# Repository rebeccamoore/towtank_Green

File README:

Section 1: An Introduction

This document serves as a comprehensive instruction manual for using the large tow-tank system in Link 280 at Syracuse University.  In this document, you will find descriptions of hardware and software.  It is the goal to establish this using some type of revision software.  The original document was maintained on github @ github.com/johndannenhoffer.

1.1: Document use

This document serves as a simple instruction manual for using the large tow-tank system in Link 280 at Syracuse University.  This was originally prepared by John Dannenhoffer IV.  To make changes, please indicate your name and contact information in the authors list (below) and specify which sections you contributed (and at what time these contributions were made).  If you have any questions regarding material, please direct your questions towards the most recent author of a section.  

1.1.2: Comments and plans for revision
Comments or plans for revisions will be presented using c-style comments.  This means that lines are commented using "//" and whole blocks of comments are denoted using a leading "/*" and a trailing "*/"

E.G.
This is a fake section to show commenting conventions used in this document.
//If you would like to commend a line, do so like this.

This is a list of things that will change over time.  So far we have…
foo
bar
foobar
/* this is something I plan to add later and finalize, but isn't currently finished yet
This is also something that should be continued */

1.1.3: Revision control software

By using revision control software, a document that goes through a number of changes can be maintained such that if undesirable changes are made, one can go back to previous versions.  Also, size is reduced by not having to keep archived files.  A free and easy to use software that implements revision control is Git and it's website github.com.  NOTE: To be free, an accounts material must remain open to the public.  This may be undesirable in the future.  There are two ways to use this software.  You can either download git to your local computer and manage your files (called repositories) that way or you can upload and download content through the web while logged into your account.

Branching: To change a document for your own purposes, create a branch from some node of the project.  Go to github.com to learn about this process.

Section 1.2 Authors

John Dannenhoffer IV (JFD4)
315-256-3521
johndannenhoffer@gmail.com

Summer research student for the summer of 2012.  Original author

Revision History
8/20/2012 - Created document and added sections 1,2,3, and 4 (JFD4)
//10/6/2012 - Added pictures of hardware (JFD4)

Section 1.2: Contents

This document contains a number of sections which describe different parts of the system (hardware, software, instructions,...)

1. Introduction:  Describes the use and maintenance of this document and its contents.

2. Running the tow tank:  A quick how-to guide to operating the tow tank.

3. Tow tank hardware:  The main hardware components are explained here

4. Tow tank software. The software used to run and gather data from the tow tank is described here

/* To be added later
5. PIV.  The components used for flow visualization are described here

6. Beginning Electronics for Experimentalists: This serves as a guide to electronics for experimentalists, especially those not 

7. Instrumentation for Experimentalists: A brief description of instrumentation techniques useful for the experimentalist.  This and the next section are geared towards experimentalists working in fluid mechanics

8. Actuation for Experimentalists: A description of actuation techniques useful for the experimentalist.  Microcontrollers, DC Motors, solenoids, servos, LEDs, MOSFETs and H-Bridge drivers, amplifiers, and much more will be discussed.  This section, along with sections 5 can serve as a guide to designing actuation system for experimental use.

9. Electronics Fabrication for Experimentalist:  This section describes experiential knowledge on different techniques to setup electronic apparatus for use in a lab setting.  Breadboarding, prototyping, soldering, and PCB (printed circuit board) production are discussed.

10. Purchasing: Specific vendors and purchasing techniques for everything electronic are discussed here.  Take this section with a grain of salt, as the electronics landscape changes very quickly.

*/

Section 2: Running the tow tank

This section describes the basics of running the tow tank.

2.1: What is needed to run the tow tank?

To run the tow tank, the following is needed to run the tow tank.

-Arduino hardware.  An Arduino is a micro controller development board which is used for quick prototyping of embedded systems.  Digital and analog signals from hardware can interfaced with software written in an easy to write c-based language.  The Arduino board (there are a number of generations of boards with slight differences) has header pin outputs for almost all of its pins.  This allows the user to connect peripherals to the Arduino such a digital signals, analog signals, serial signals, power,…  The board that was used for the first generation of the tow tank was the Arduino Uno.  Also, because there is a large Arduino community, a number of open source hardware and software tools have been developed.  Supplementary hardware which are attached on top of an Arduino are called shields.  These can serve many purposes.  Also, a number of software libraries have been developed to do various things within software, such as numerical calculations, interfacing with certain hardware,…  This project uses one shield (below) and its corresponding library.

-Arduino Software.  This is software that is used to communicate between a computer and the micro controller development board (Arduino).  Go to http://arduino.cc/en/Main/Software to download the latests version of the software. The Arduino software contains three important things.  1) An IDE (integrated development environment) to write and compile code in. 2) Drivers to communicate with the Arduino.  This allows you to upload your code onto the board.  It also allows for serial communication. 3) A serial monitor.  This allows the user to monitor the serial communication between the Arduino hardware and the computer.  This can be used very effectively as a debugging tool.

-A power source.  You need a way to power the power electronics in the tow tank system.  An ATX power supply and breakout board is used for this purpose.

-Pololu motor driver shield.  This "shield" is used in order to allow an Arduino to switch large amounts of current on an off.  http://www.pololu.com/catalog/product/2502  .  This shield plugs into the Arduino on top (it will only fit one way).  Through the connections with the Arduino, the program running on the Arduino controls the hardware on the shield and through this hardware, can control large amounts of current.  We use this to drive the motors for the tow tank.

-Pololu motor driver shield library.  To control the motor driver shield, software needs to be written on the Arduino.  Because interfacing with the shield is not trivial, a software library has been developed to make interfacing with the shield easier.  This allows simple function calls in your code to control the shield.  Go to https://github.com/pololu/Dual-VNH5019-Motor-Shield to download the zip file (click the "zip" button next to the "http" button.   Unzip this file.  Move the folder "DualVNH5019MotorShield" to the appropriate folder which holds your Arduino libraries.  On a mac, the directory would be ~/Documents/Arduino/libraries/. On Windows, it would be My Documents\Arduino\libraries .  NOTE:  If this is the first library that you are adding, you may need to create the "libraries" folder in the appropriate place.  When you launch the Arduino application, and you click the "Sketch" drop down and "Import Libraries", you should see the DualVNH5019-Motor-Shield as an option.  If you click this, it should add the line #include "DualVNH5019-Motor-Shield.h" to the top of your code.

-(OPTIONAL) Direction control board.  To prevent the system from causing itself harm by running the carriage into one of the sides, a control board was developed which uses 2 limit switches to limit motion.  If a limit switch is pressed, the carriage is stopped from moving in the direction of that limit switch, but can still move in the opposite direction.  See section 3.2.5 for more information on this.

2.2.1: Steps to run the tow tank w/o direction control.

Below are step by step instructions for setting up and running the tow tank.

1) Power source.  Make sure the power source is working.  Plug the 24-pin connector from the ATX power supply into the distribution board (the header is polarized).  Plug the power supply into a wall outlet and turn it on.  The fan should turn on.  NOTE: If you are using a first generation power distribution board (REV 1.0), you will need to solder together the green wire with one of the black wires.  /*This is addressed in later revisions of the boards.*/

2) Check power.  If the fan turns on, check the voltage levels of each of the outputs.  The power supply will output 4 different levels: Ground (GND), 3.3 volts (3V3), 5 volts (5V), and 12 volts (12V).  Using a multimeter in voltage mode, press the black probe to any exposed metal on the ground rail (lines denote which terminal blocks (green things) and barrier strips (black things) belong to which rail).  I suggest pressing the black probe to one of the screws in a ground (GND) terminal block.  Then take the red probe and connect it to the different rails.  The meter should read out approximately 3.3, 5.0 and 12.0 volts.  The board allows for higher voltages to be achieved by "stacking."  Refer to Section 3.2.4 for more information of this.

3) If the power is working (the fan turns on and the voltage levels seems to be correct), connect power to the motor driver shield.  To do this, connect the 12V on the power distro to the VIN of the motor driver shield and the GND to the GND.  Do this using a wire with stripped ends and the terminal blocks.  A blue LED should turn on.

4) Connect the motor to channel 1 of the motor driver shield.  Connect the output of the motor (the gray cable) to a barrier strip.  The gray cable has two spade terminal outputs.  Connect these to the long barrier strip on different strips (not across from each other).  A barrier strip connects the two connections in the same row.  From the barrier strip, connect the motor to the motor shield using a cable with a spade terminal on one end and a stripped wire on the other end.  The positive motor connection (red) should be connected to the M1A terminal connection.  The negative motor connection (black) should be connected to the M1B terminal connection.

NOTE: Using "beep" mode on the multimeter checks to see if connections are made.  The multimeter will emit a beep if a short is detected between the two probes.  This is extremely useful for checking to see if connections are securely made.

Use the multimeter to check that the positive terminal of the motor is connected to the M1A terminal and the negative terminal of the motor is connected to the M1B terminal.

IMPORTANT NOTE: IN BEGINNING TESTING, IT IS IMPORTANT TO MAKE SURE THAT THE SYSTEM DOESN'T BREAK ITSELF.  THIS MEANS THAT YOU SHOULD HAVE YOUR HAND ON THE POWER SUPPLY SWITCH DURING TESTING AND IF THE CARRIAGE APPROACHES A SIDE, TURN OFF THE POWER.  THIS IS ADDRESSED LATER WITH THE USE OF DIRECTION LIMITING CIRCUITS AND LIMIT SWITCHES, BUT UNTIL THOSE ARE PUT IN THE SYSTEM, PROCEED WITH CAUTION.

5) Test the motor.  Open the sketch (programs in Arduino are called sketches) called demo.pde (could be called demo.ino based on your version of the Arduino software downloaded).  This is in the pololu library zip file.  Connect the Arduino to the computer via USB cable (a light should go on on the Arduino) and click the upload button in the Arduino IDE (any compiling errors should be trivial and easily addressable).

6) "Plug" the shield into the Arduino.  This should fit only one way.

7) When the sketch is done uploading to the board (the yellow RX LED will flash while code is being uploaded onto the board), the system should start moving in the manner implemented in demo.pde.  The default (if you don't change any of the code) is to go one direction for ~1 second, speeding up along the way.  Then slow down for ~1 second to 0.  Then do the same thing in the opposite direction.  The motor should then stop for ~4 seconds.  This will then repeat.

2.2.2 Steps for running the tow tank w/ direction control:

Once the operation of the system is verified w/o direction control, implement the direction control.  This uses the direction control boards (small ~5cmx~5cm boards with 2 relays and other components) and 2 limit switches.

The steps for doing this are basically the same, but with 1 difference.  The motor must be put in series with the direction control circuit.  The workings of this control circuit are described in section 3.2.? but the basic idea is that if a limit switch is depressed, the motor can not move in a direction that would damage the system.  

To do this, take the connection between M1A and the barrier strip and "insert" the direction control circuit in this connection.

The only connection that is different for this setup is the connection between M1A and the barrier strip.  The new connections should be as follows.

-The positive terminal on the barrier strip (red spade terminal) should be connected to the CON1 screw terminal on the direction control board.  
-The CON2 screw terminal should be connected to the M1A connection on the motor driver shield.  
-Connect 12V and Ground to the board's screw terminal power connections.  

The board will allow current to flow only if the connection to the limit switch is closed (connected).  The connections to the limit switches are one the 4x1 header pin on the direction control board.  The 1 and 2 pins control 1 direction and the 3 and 4 pins control the other direction.  The wiring for this connector is described in Section 3.2.5

This means that to move in both directions, both 1 and 2 as well as 3 and 4 should be shorted.  To test this (without connecting the limit switches), use some metal object to short pins 1 and 2 and pins 3 and 4 (NOTE: It is ok to short 2 and 3 as well).

One easy way to test this setup is to use some metal object and short pins 1 and 2 while running the demo program.  The carriage should move in one direction as expected, but not the other.  Then short 3 and 4 and the carriage should move in the other direction.

NOTE:  Because the direction control board uses electromechanical relays, you will hear a click when you either make or break a connection (between 1 and 2 or 3 and 4).  This is perfectly normal.  However, you should only hear one click and if you hear multiple clicks that continue, the connection between the pins to be shorted is wrong.  Placing a precision screwdriver or allan wrench in the gap is a good way to make sure that the connection is correct.

IF EVERYTHING FUNCTIONS AS EXPECTED, THE HARDWARE SHOULD ALL BE WORKING AND YOU CAN MOVE FORWARD WITH PROGRAMMING!!!

Section 3 : Tow Tank Hardware

3.1: Physical hardware

3.1.1: The tank

3.1.2: Water containment

3.2: Electronic Hardware

3.2.1: Motor

3.2.2: Motor tachometer

3.2.3: Carriage Tachometer

3.2.4: Power distribution board

3.2.5: Direction Control Board

3.2.6: Arduino

3.2.7: Pololu Motor Driver Shield

3.2.8: Level Shifter

Section 4 : Tow Tank Software

4.1: Control software

4.1.1: Arduino

4.1.2: Pololu Motor Driver Shield Library

4.1.3: Level shifter arduino library

4.1.4: Test programs

4.1.5: Serial GUI

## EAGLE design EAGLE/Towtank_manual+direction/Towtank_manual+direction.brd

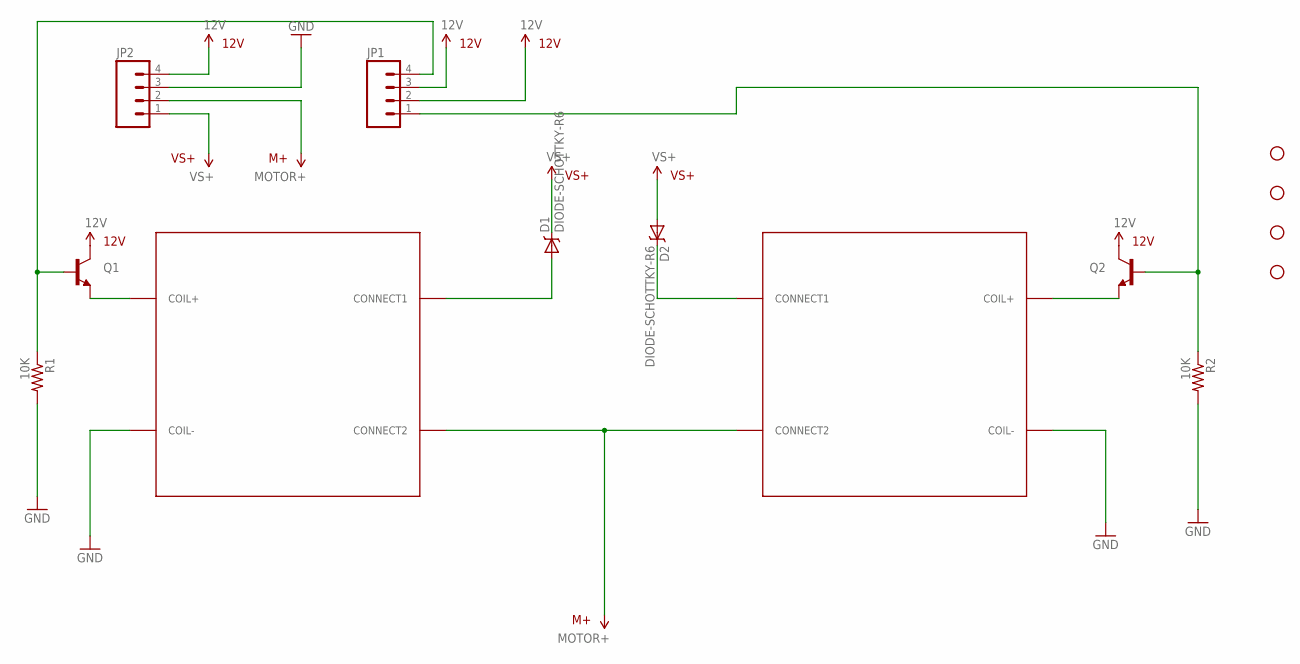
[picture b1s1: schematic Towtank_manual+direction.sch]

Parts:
D1, D2: DIODE-SCHOTTKY-R6; R6-AXIAL
JP1: M04LOCK_LONGPADS; 1X04_LOCK_LONGPADS
JP2: M04SCREW_LOCK; SCREWTERMINAL-3.5MM-4_LOCK
JP3, JP4, JP5, JP6: STAND-OFF
Q1, Q2: TRANSISTOR_NPNTO-92-AMMO; TO-92-AMMO
R1, R2: 10K; AXIAL-0.4
U1, U2: G5LE-1A4_SPST-NO; PC-PIN

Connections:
12V: JP1.2, JP1.3, JP2.4, Q1.3 (C), Q2.3 (C)
GND: JP2.3, R1.P$2 (2), R2.P$2 (2), U1.COIL-, U2.COIL-
MOTOR+: JP2.2, U1.CONNECT2, U2.CONNECT2
unnamed: D1.P$ANODE (ANODE), U1.CONNECT1
unnamed: D2.P$CATHODE (CATHODE), U2.CONNECT1
unnamed: JP1.4, Q1.2 (B), R1.P$1 (1)
unnamed: JP1.1, Q2.2 (B), R2.P$1 (1)
unnamed: Q1.1 (E), U1.COIL+
unnamed: Q2.1 (E), U2.COIL+
VS+: D1.P$CATHODE (CATHODE), D2.P$ANODE (ANODE), JP2.1

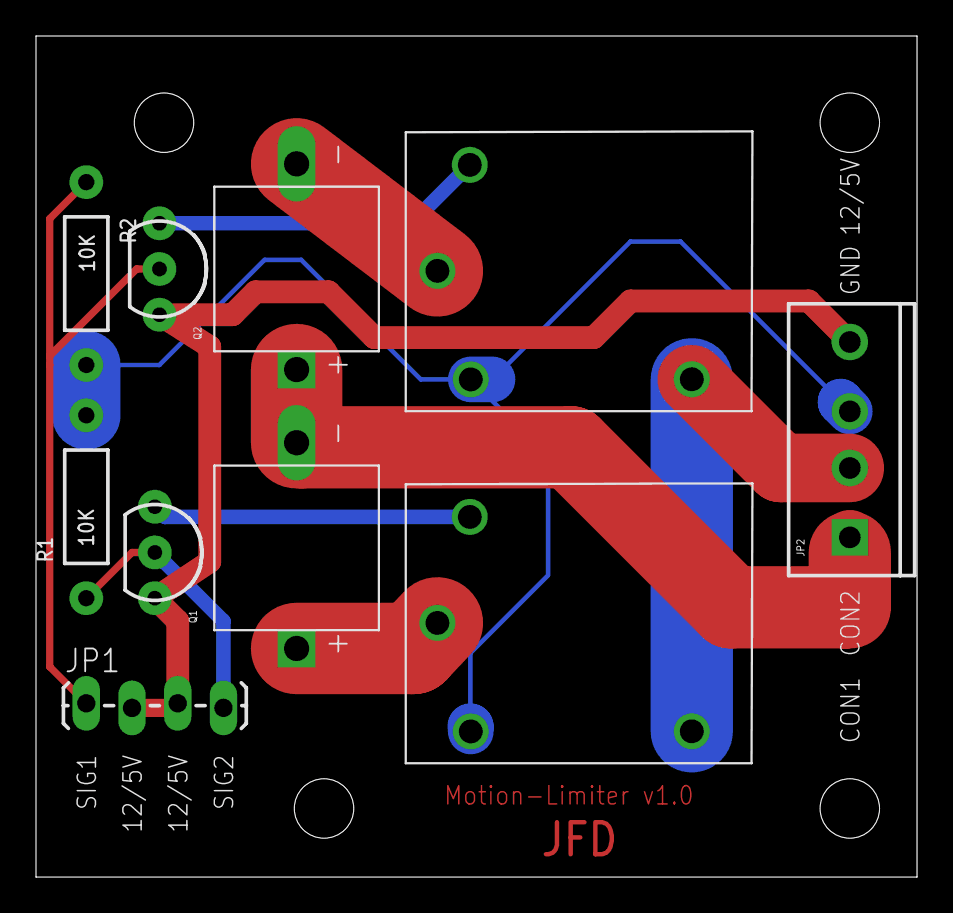
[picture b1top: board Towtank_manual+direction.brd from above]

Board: 2 copper layers, 48.9 x 46.7 mm, 14 parts (0 on the bottom side), 10 nets.

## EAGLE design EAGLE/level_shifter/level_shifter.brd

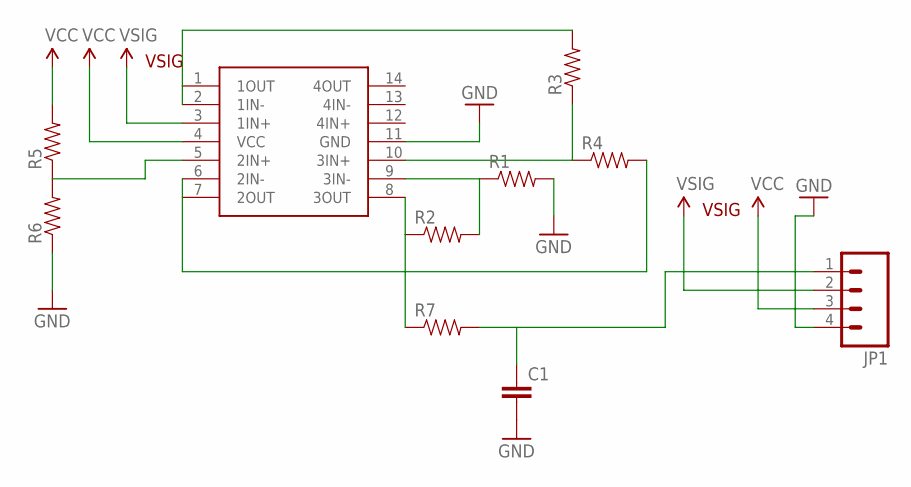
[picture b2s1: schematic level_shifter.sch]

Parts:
C1: CAPPTH1; CAP-PTH-5MM
JP1: M04SCREW-5MM; SCREWTERMINAL-5MM-4
R1, R2, R3, R4, R5, R6, R7: RESISTORPTH-1/4W; AXIAL-0.4
U$1: LM324DIP; DIL14

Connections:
GND: C1.2, JP1.4, R1.P$2 (2), R6.P$1 (1), U$1.11 (GND)
unnamed: R3.P$2 (2), U$1.1 (1OUT), U$1.2 (1IN-)
unnamed: C1.1, JP1.1, R7.P$2 (2)
unnamed: R4.P$2 (2), U$1.6 (2IN-), U$1.7 (2OUT)
unnamed: R3.P$1 (1), R4.P$1 (1), U$1.10 (3IN+)
unnamed: R5.P$1 (1), R6.P$2 (2), U$1.5 (2IN+)
unnamed: R1.P$1 (1), R2.P$2 (2), U$1.9 (3IN-)
unnamed: R2.P$1 (1), R7.P$1 (1), U$1.8 (3OUT)
VCC: JP1.3, R5.P$2 (2), U$1.4 (VCC)
VSIG: JP1.2, U$1.3 (1IN+)

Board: 2 copper layers, 10 parts (0 on the bottom side), 10 nets, no tracks yet.

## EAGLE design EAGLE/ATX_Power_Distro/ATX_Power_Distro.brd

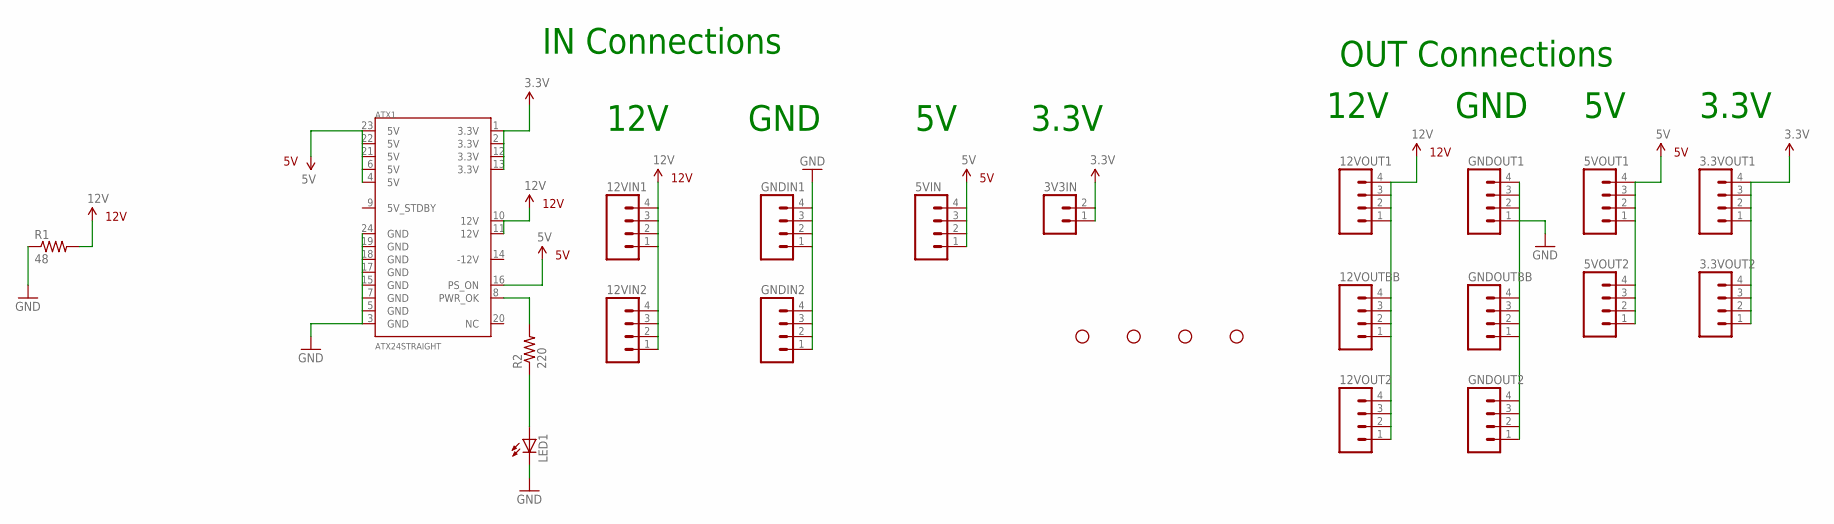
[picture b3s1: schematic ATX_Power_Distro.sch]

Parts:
3.3VOUT1, 3.3VOUT2, 5VIN, 5VOUT1, 5VOUT2, 12VIN1, 12VIN2, 12VOUT1, 12VOUT2: M04SCREW-5MM; SCREWTERMINAL-5MM-4
3V3IN: M025MM; SCREWTERMINAL-5MM-2
12VOUTBB: M04BARRIER_BLOCK_0.375"; 1X04_BARRIER_BLOCK_0.375"
ATX1: ATX24STRAIGHT; ATX_24
GNDIN1, GNDIN2: M04SCREW-5MM; SCREWTERMINAL-5MM-4
GNDOUT1, GNDOUT2: M04SCREW-5MM; SCREWTERMINAL-5MM-4
GNDOUTBB: M04BARRIER_BLOCK_0.375"; 1X04_BARRIER_BLOCK_0.375"
JP1, JP2, JP3, JP4: STAND-OFF
LED1: LED1206; LED-1206
R1: 48; TO220-2PIN
R2: 220; 1206

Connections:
3.3V: 3.3VOUT1.1, 3.3VOUT1.2, 3.3VOUT1.3, 3.3VOUT1.4, 3.3VOUT2.1, 3.3VOUT2.2, 3.3VOUT2.3, 3.3VOUT2.4, 3V3IN.1, 3V3IN.2, ATX1.1 (3.3V), ATX1.2 (3.3V), ATX1.12 (3.3V), ATX1.13 (3.3V)
5V: 5VIN.1, 5VIN.2, 5VIN.3, 5VIN.4, 5VOUT1.1, 5VOUT1.2, 5VOUT1.3, 5VOUT1.4, 5VOUT2.1, 5VOUT2.2, 5VOUT2.3, 5VOUT2.4, ATX1.4 (5V), ATX1.6 (5V), ATX1.16 (PS_ON), ATX1.21 (5V), ATX1.22 (5V), ATX1.23 (5V)
12V: 12VIN1.1, 12VIN1.2, 12VIN1.3, 12VIN1.4, 12VIN2.1, 12VIN2.2, 12VIN2.3, 12VIN2.4, 12VOUT1.1, 12VOUT1.2, 12VOUT1.3, 12VOUT1.4, 12VOUT2.1, 12VOUT2.2, 12VOUT2.3, 12VOUT2.4, 12VOUTBB.1, 12VOUTBB.2, 12VOUTBB.3, 12VOUTBB.4, ATX1.10 (12V), ATX1.11 (12V), R1.2
GND: ATX1.3 (GND), ATX1.5 (GND), ATX1.7 (GND), ATX1.15 (GND), ATX1.17 (GND), ATX1.18 (GND), ATX1.19 (GND), ATX1.24 (GND), GNDIN1.1, GNDIN1.2, GNDIN1.3, GNDIN1.4, GNDIN2.1, GNDIN2.2, GNDIN2.3, GNDIN2.4, GNDOUT1.1, GNDOUT1.2, GNDOUT1.3, GNDOUT1.4, GNDOUT2.1, GNDOUT2.2, GNDOUT2.3, GNDOUT2.4, GNDOUTBB.1, GNDOUTBB.2, GNDOUTBB.3, GNDOUTBB.4, LED1.C, R1.1
unnamed: ATX1.8 (PWR_OK), R2.2
unnamed: LED1.A, R2.1

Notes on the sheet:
IN Connections
OUT Connections
12V
3.3V
GND

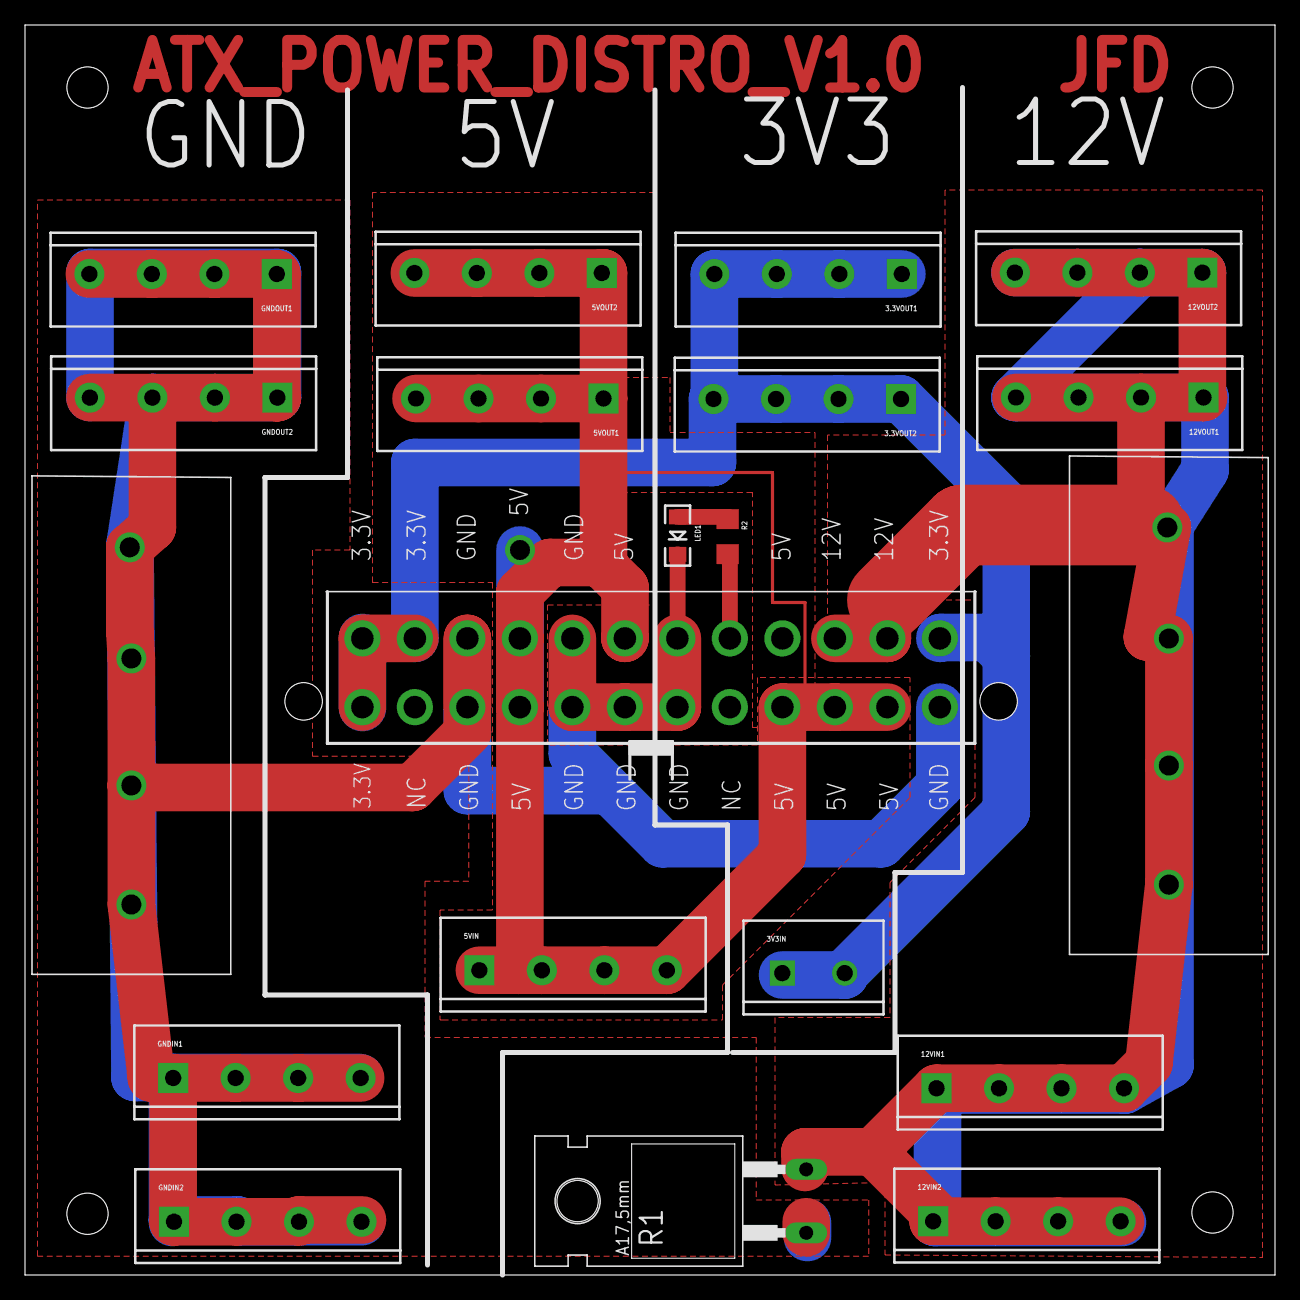
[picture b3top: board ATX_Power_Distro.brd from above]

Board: 2 copper layers, 100.0 x 100.0 mm, 24 parts (0 on the bottom side), 6 nets.

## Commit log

2012-08-24 second commit
2012-08-24 third commit
2012-08-24 fourth comment
2012-08-24 add section 2
2012-08-24 update Section2
2012-10-05 Simple directions to get the tow tank working
2012-10-05 Changed section2 to section3

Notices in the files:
parts and their libraries:
SparkFun: Licensing: CC v3.0 Share-Alike You are welcome to use this library for commercial purposes.
